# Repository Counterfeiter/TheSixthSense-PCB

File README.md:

TheSixthSense Schematic and PCB Files
==============

License
--------------
OSH - GPLv2

Software
--------------
Free Version of CADSoft Eagle v6 (.1)

Included
--------------
- versions history
- schematic
- PCB design
- Images

Schematic:
--------------

Board design:
--------------

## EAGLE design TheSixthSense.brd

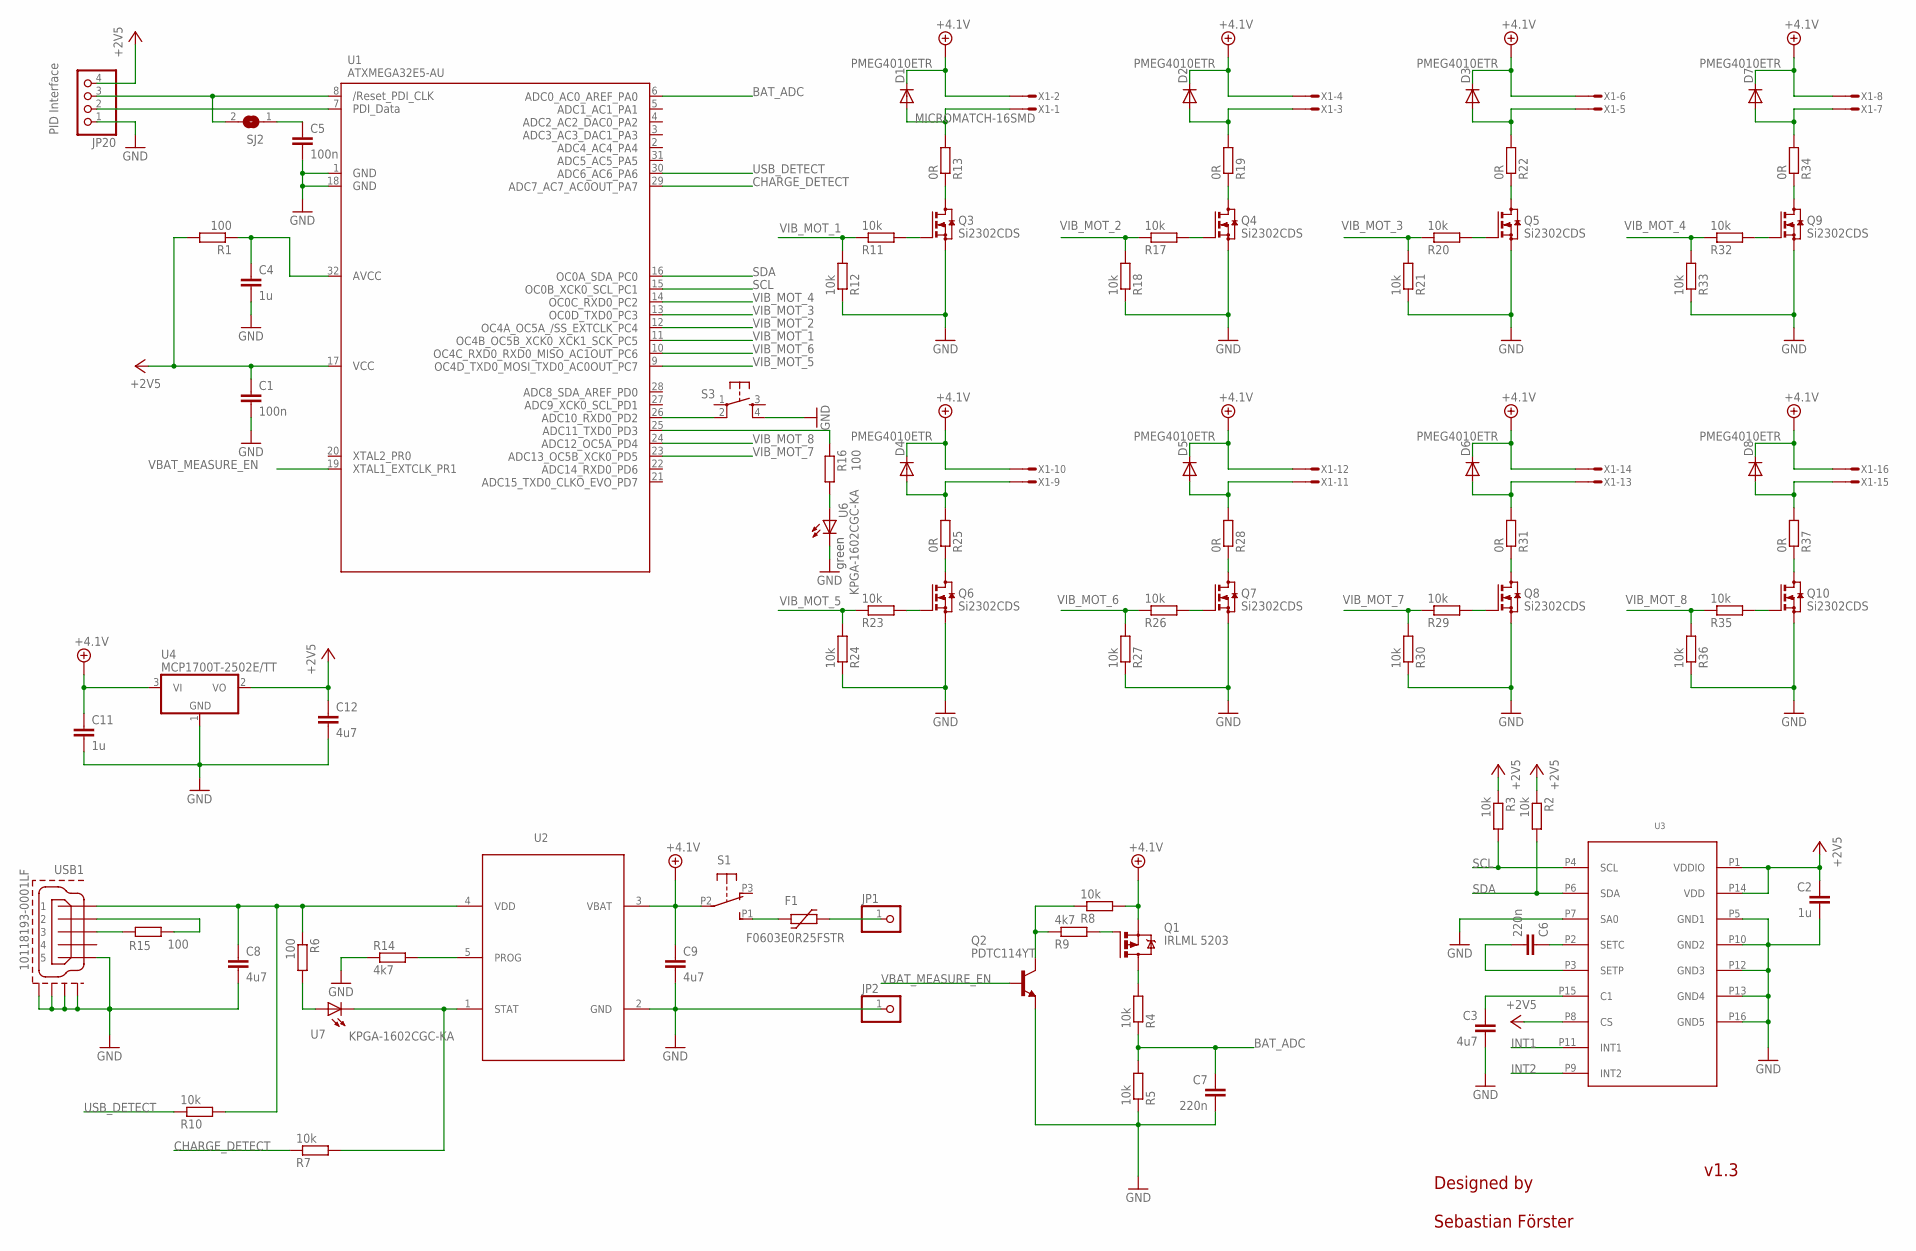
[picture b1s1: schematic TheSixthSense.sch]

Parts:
C1, C5: 100n; C0603
C2, C4, C11: 1u; C0603
C3, C8, C9, C12: 4u7; C0603
C6, C7: 220n; C0603
D1, D2, D3, D4, D5, D6, D7, D8: PMEG4010ETR; SOD123
F1: F0603E0R25FSTR; R0603
JP1, JP2: PINHD-1X1; 1X01
JP20: PINHD-1X4_2.00; 1X04M
Q1: IRLML 5203; MICRO3
Q2: PDTC114YT; SOT23
Q3, Q4, Q5, Q6, Q7, Q8, Q9, Q10: Si2302CDS; SOT23
R1, R6, R15, R16: 100; R0603
R2, R3, R4, R5, R7, R8, R10, R11, R12, R17, R18, R20, R21, R23, R24, R26, R27, R29, R30, R32, R33, R35, R36: 10k; R0603
R9, R14: 4k7; R0603
R13, R19, R22, R25, R28, R31, R34, R37: 0R; R0603
S1: ALPSSSSS811101; SSSS811101
S3: 10-XX; SKSCLAE010
SJ2: SJ
U1: ATXMEGA32E5-AU; TQFP32-08
U2: MCP73831; SOT23-5L
U3: LSM303D; LGA3X3_16L
U4: MCP1700T-2502E/TT; SOT23
U6, U7: KPGA-1602CGC-KA; CHIP-LED0603
USB1: 10118193-0001LF; MOLEX-47364-0001
X1: MICROMATCH-16SMD

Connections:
+3V3: C1.1, C2.1, C12.1, JP20.4, R1.2, R2.1, R3.1, U1.17 (VCC3), U3.P1 (VDDIO), U3.P8 (CS), U3.P14 (VDD), U4.2 (VO)
+4.1V: C9.1, C11.1, D1.C, D2.C, D3.C, D4.C, D5.C, D6.C, D7.C, D8.C, Q1.2 (S), R8.2, S1.P2, U2.3 (VBAT), U4.3 (VI), X1.1, X1.3, X1.5, X1.7, X1.9, X1.11, X1.13, X1.15
BAT_ADC: C7.1, R4.1, R5.2, U1.6 (PA0)
CHARGE_DETECT: R7.1, U1.29 (PA7)
GND: C1.2, C2.2, C3.2, C4.2, C5.2, C7.2, C8.2, C9.2, C11.2, C12.2, JP2.1, JP20.1, Q2.2 (E), Q3.2 (S), Q4.2 (S), Q5.2 (S), Q6.2 (S), Q7.2 (S), Q8.2 (S), Q9.2 (S), Q10.2 (S), R5.1, R12.1, R14.1, R18.1, R21.1, R24.1, R27.1, R30.1, R33.1, R36.1, S3.4 (S1), U1.1 (GND1), U1.18 (GND2), U2.2 (GND), U3.P5 (GND1), U3.P7 (SA0), U3.P10 (GND2), U3.P12 (GND3), U3.P13 (GND4), U3.P16 (GND5), U4.1 (GND), U6.C, USB1.5, USB1.GND1, USB1.GND2, USB1.GND3, USB1.GND4
GPS_ENABLE: Q2.3 (C), R8.1, R9.1
INT1: U3.P11 (INT1)
INT2: U3.P9 (INT2)
unnamed: C6.2, U3.P3 (SETP)
unnamed: Q1.3 (D), R4.2
unnamed: C3.1, U3.P15 (C1)
unnamed: C6.1, U3.P2 (SETC)
unnamed: F1.1, S1.P1 (S)
unnamed: R6.2, U7.A
unnamed: C8.1, R6.1, R10.2, U2.4 (VDD), USB1.1
unnamed: C5.1, SJ2.1
unnamed: C4.1, R1.1, U1.32 (AVCC)
unnamed: JP20.3, SJ2.2, U1.8 (RESET)
unnamed: JP20.2, U1.7 (PDI_DATA)
unnamed: R14.2, U2.5 (PROG)
unnamed: R15.1, USB1.3
unnamed: Q1.1 (G), R9.2
unnamed: Q3.1 (G), R11.2
unnamed: Q3.3 (D), R13.1
unnamed: D1.A, R13.2, X1.16
unnamed: R15.2, USB1.2
unnamed: Q4.1 (G), R17.2
unnamed: Q4.3 (D), R19.1
unnamed: D2.A, R19.2, X1.14
unnamed: Q5.1 (G), R20.2
unnamed: Q5.3 (D), R22.1
unnamed: D3.A, R22.2, X1.12
unnamed: Q6.1 (G), R23.2
unnamed: R16.2, U6.A
unnamed: Q6.3 (D), R25.1
unnamed: D4.A, R25.2, X1.8
unnamed: Q7.1 (G), R26.2
unnamed: Q7.3 (D), R28.1
unnamed: D5.A, R28.2, X1.6
unnamed: Q8.1 (G), R29.2
unnamed: Q8.3 (D), R31.1
unnamed: D6.A, R31.2, X1.4
unnamed: F1.2, JP1.1
unnamed: S3.2 (P1), U1.26 (PD2)
unnamed: R16.1, U1.25 (PD3)
unnamed: Q9.1 (G), R32.2
unnamed: Q9.3 (D), R34.1
unnamed: D7.A, R34.2, X1.10
unnamed: Q10.1 (G), R35.2
unnamed: Q10.3 (D), R37.1
unnamed: D8.A, R37.2, X1.2
NNNN: R7.2, U2.1 (STAT), U7.C
SCL: R3.2, U1.15 (PC1), U3.P4 (SCL)
SDA: R2.2, U1.16 (PC0), U3.P6 (SDA)
USB_DETECT: R10.1, U1.30 (PA6)
VBAT_MEASURE_EN: Q2.1 (B), U1.19 (PR1)
VIB_MOT_1: R11.1, R12.2, U1.11 (PC5)
VIB_MOT_2: R17.1, R18.2, U1.12 (PC4)
VIB_MOT_3: R20.1, R21.2, U1.13 (PC3)
VIB_MOT_4: R32.1, R33.2, U1.14 (PC2)
VIB_MOT_5: R23.1, R24.2, U1.9 (PC7)
VIB_MOT_6: R26.1, R27.2, U1.10 (PC6)
VIB_MOT_7: R29.1, R30.2, U1.23 (PD5)
VIB_MOT_8: R35.1, R36.2, U1.24 (PD4)

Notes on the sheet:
PID Interface
Designed by
Sebastian Förster
green
v1.3

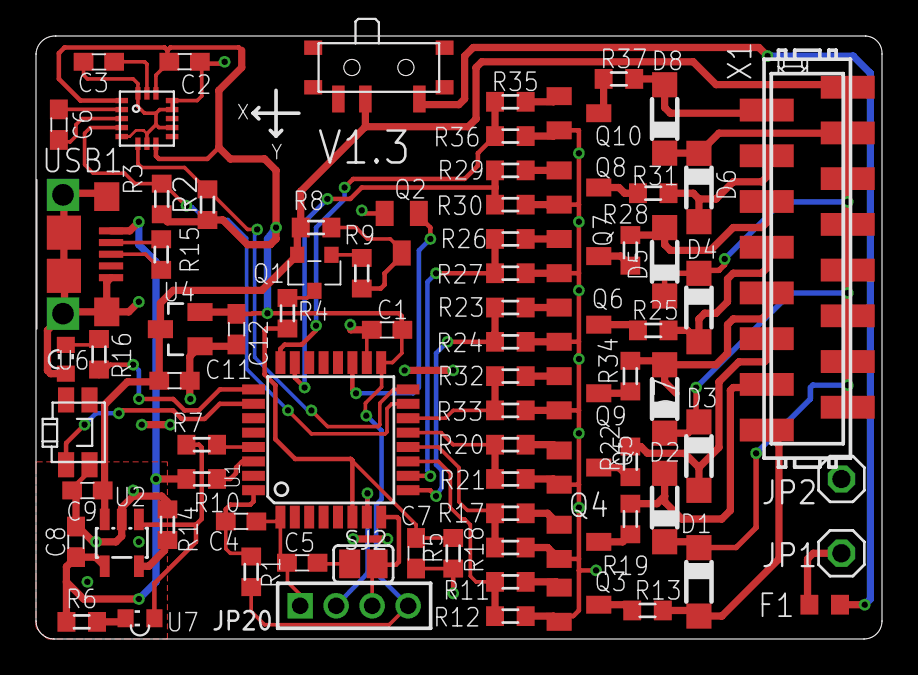
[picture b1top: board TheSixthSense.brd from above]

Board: 2 copper layers, 47.0 x 33.5 mm, 81 parts (0 on the bottom side), 62 nets.

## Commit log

2015-04-28 init commit
2015-04-28 add License and images
2015-05-24 - adding images to readme.md
2015-06-09 New 8 motor support! - adding motor 5&6: µC <-> Mosfets
2015-06-20 - new version v1.3 - add a push button - add a fuse - add a switch to disconnect the battery - add a new motor connector
2015-08-10 - new mouser part list for pcb v1.3
